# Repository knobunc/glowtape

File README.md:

# Glowtape

Glow-in-the-dark display, 64 pixels wide, and as long as the memory allows :)

Using a UV LED pixel illumination from the [Glowxels](http://glowxels.org)
project.

[Note: this is pretty much work in progress and not the final version.]

To build: get all dependencies (if you're using nix, or the nix package manager,
it is simplest, they are in shell.nix).
Mostly openscad for the case, rp2040 sdk and toolchain for the firmware,
[bdfont.data](https://github.com/hzeller/bdfont.data) to compactly encode fonts
used in the firmware and the [gcode-cli](https://github.com/hzeller/gcode-cli)
used in the [set-time utility](./set-time.sh).

  * [casing/](./casing/) for the OpenSCAD case 
  * [firmware/](./firmware/) contains the firmware.
  * [Gloxwls PCB](http://glowxels.org/). Check out the ['narrow'](https://github.com/hzeller/glowxels/tree/feature-20240902-narrow) feature branch.
  * [Encoder PCB](./pcb/encoder/) to pick up the encoder tape.
    Just type `make` to generate the fab files.
  * The sync-tape to be stuck to the back of the 50mm glow-in-dark
    tape: just `make` in the toplevel directory, it creates the PDF from
    the hand-written PostScript. Print on a high-resolution printer
    (e.g. 1200dpi) to minimize line-thickness variations due to aliasing.
  * Also some glow-in-dark tape that you can find in a hardware store, e.g.
    something like [this](https://www.amazon.com/gp/product/B076BMQHXB)
    (no affiliation).

The RP2040 RTC does not remember its time after a reset (meh), so you need to
call the `./set-time.sh` script after a flash or reset/battery outage.

## Action shot

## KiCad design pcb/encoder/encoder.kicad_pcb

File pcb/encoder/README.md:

Encoder PCB.

Note, this looks like one PCB, but you need to cut it in half in the middle at
the line.

Single-sided, so easy to etch at home.

For better contrast, I laser-cut a dark thin tape with two 0.4mm slots, 2mm
apart and taped on the photo transistor.

The strip-pattern is picked up with one photo transistor picking up a dark
strip, the other the light strip. When the tape is moved, the light conditions
swap. So the differntial pick-up makes it resilient to environment light
conditions as there does not need to be a fixed cut-off.

Choose resistors as needed; For `R9` LED, 82Ω was used. The `R1`, `R2` photo
transistor resistors, 2.7kΩ, `R5`: 10kΩ, and `R6`, which makes the whole
circuit a Schmitt Trigger for confident switch detection, somehing like 180kΩ.

Here, a home-made isolation etch:

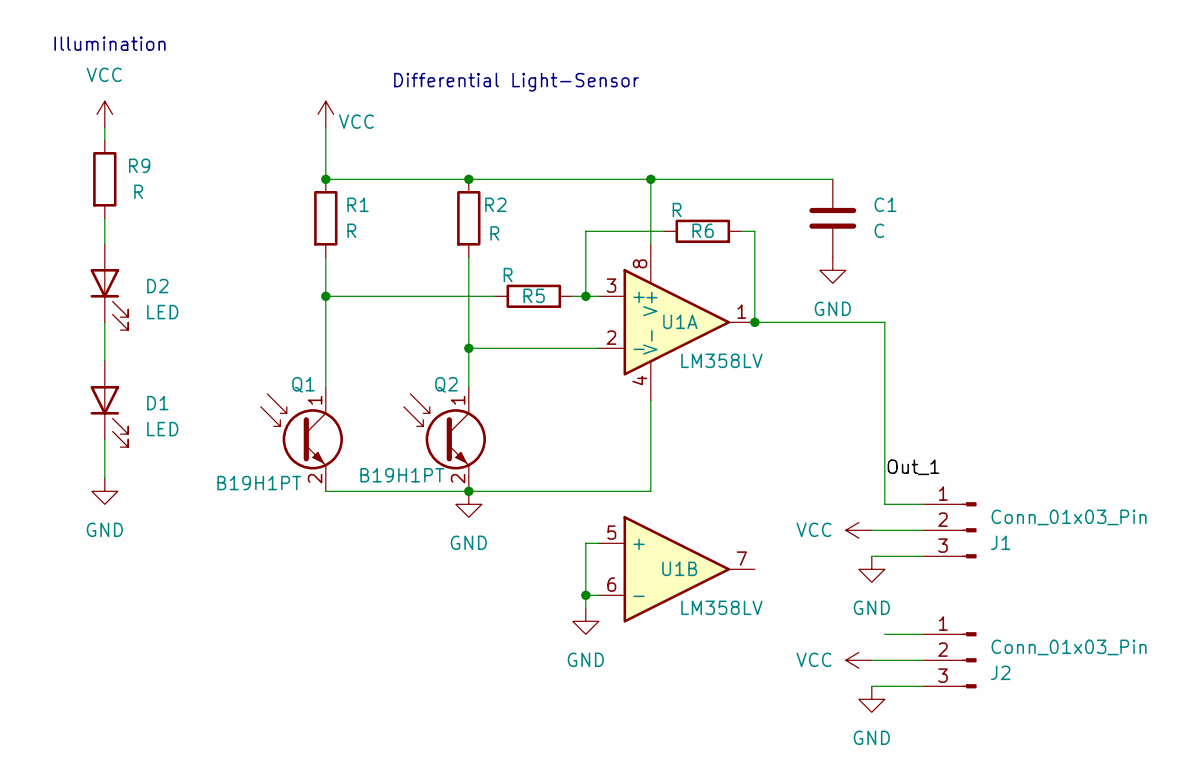
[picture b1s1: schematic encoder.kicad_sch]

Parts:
C1: C; C_0603_1608Metric
D1, D2: LED; LED_0603_1608Metric
J1, J2: Conn_01x03_Pin; PinSocket_1x03_P1.27mm_Vertical
Q1, Q2: B19H1PT; LED_0603_1608Metric
R1, R2, R5, R6, R9: R; R_0603_1608Metric
U1: LM358LV; SOT-23-8

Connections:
/Out_1: J1.1, R6.2, U1.1
GND: C1.2, D1.1 (K), J1.3, J2.3, Q1.2 (E), Q2.2 (E), U1.4 (V-), U1.5 (+), U1.6 (-)
unnamed: D1.2 (A), D2.1 (K)
unnamed: D2.2 (A), R9.2
unnamed: Q1.1 (C), R1.2, R5.1
unnamed: Q2.1 (C), R2.2, U1.2 (-)
unnamed: R5.2, R6.1, U1.3 (+)
VCC: C1.1, J1.2, J2.2, R1.1, R2.1, R9.1, U1.8 (V+)

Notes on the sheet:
Differential Light-Sensor
Illumination

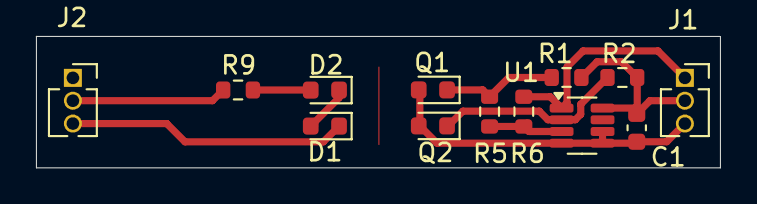
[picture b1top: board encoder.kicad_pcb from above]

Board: 2 copper layers, 38.0 x 7.3 mm, 13 parts (0 on the bottom side), 8 nets.

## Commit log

2024-10-18 Playing with optical pickup of sync-stripes.
2024-10-25 Add initial firmware experiment.
2024-10-28 Update to separate pick-up and illumination.
2024-10-28 += pstoedit to create dxf from postscript.
2024-10-28 Switch board to feather.
2024-10-29 Map bits to the new gloxel output.
2024-10-29 Read line encoder.
2024-10-29 Add another image.
2024-10-30 case, WIP
2024-10-30 Let rp2040 sit flat.
    That also allows to wedge the board in a bracket.
2024-10-30 Tiny adaption.
2024-10-31 More space for sensor board.
2024-10-31 Move encoder pin to gpio7
2024-10-31 Update comments; different distance for tape width.
2024-10-31 Don't emit image when moving fast.
2024-10-31 Basic text support. Switch content on button.
2024-10-31 Print out actual time.
2024-10-31 Make RTC time settable via serial.
2024-11-01 Re-org a bit: move periphearls into separate headers.
2024-11-01 Make sync-tape 11"x17"
2024-11-01 More space between letters, avoid dead pixels.
2024-11-01 Name after first button press.
2024-11-02 Add qr code. Allow for faster default tape movement.
2024-11-02 Add sideways banner.
2024-11-02 Better debouncing.
2024-11-02 Provide gcode-cli and bdfont-data in shell.nix
    These tools are not installed everywhere.
2024-11-02 Add large font data.
2024-11-02 Add 3D board view.
2024-11-02 Update README.
2024-11-02 Document sync-tape print.
2024-11-02 No need to put pdf in fab/
2024-11-02 Add README
2024-11-02 Fix render link.
2024-11-02 Generate bdfont support from datagen.
    Also: simplify serial line reader and prevent buffer overflow.
2024-11-02 Run format.
2024-11-02 Add .gitignore
2024-11-02 Document shell.nix better
2024-11-02 Fix comment typos.
2024-11-03 Some README refinements.
2024-11-04 Attempt to make binary smaller.
    (no success yet)
2024-11-04 Don't store unnecessary whitespace in bitmaps.
2024-11-06 Use c++17 capabilities.
    std::byteswap() was the only reason we needed c++23.
2024-11-06 Use long name weekdays.
    With some dead pixels fixed, they look now nice.
2024-11-19 Typo fix soemthing -> something
